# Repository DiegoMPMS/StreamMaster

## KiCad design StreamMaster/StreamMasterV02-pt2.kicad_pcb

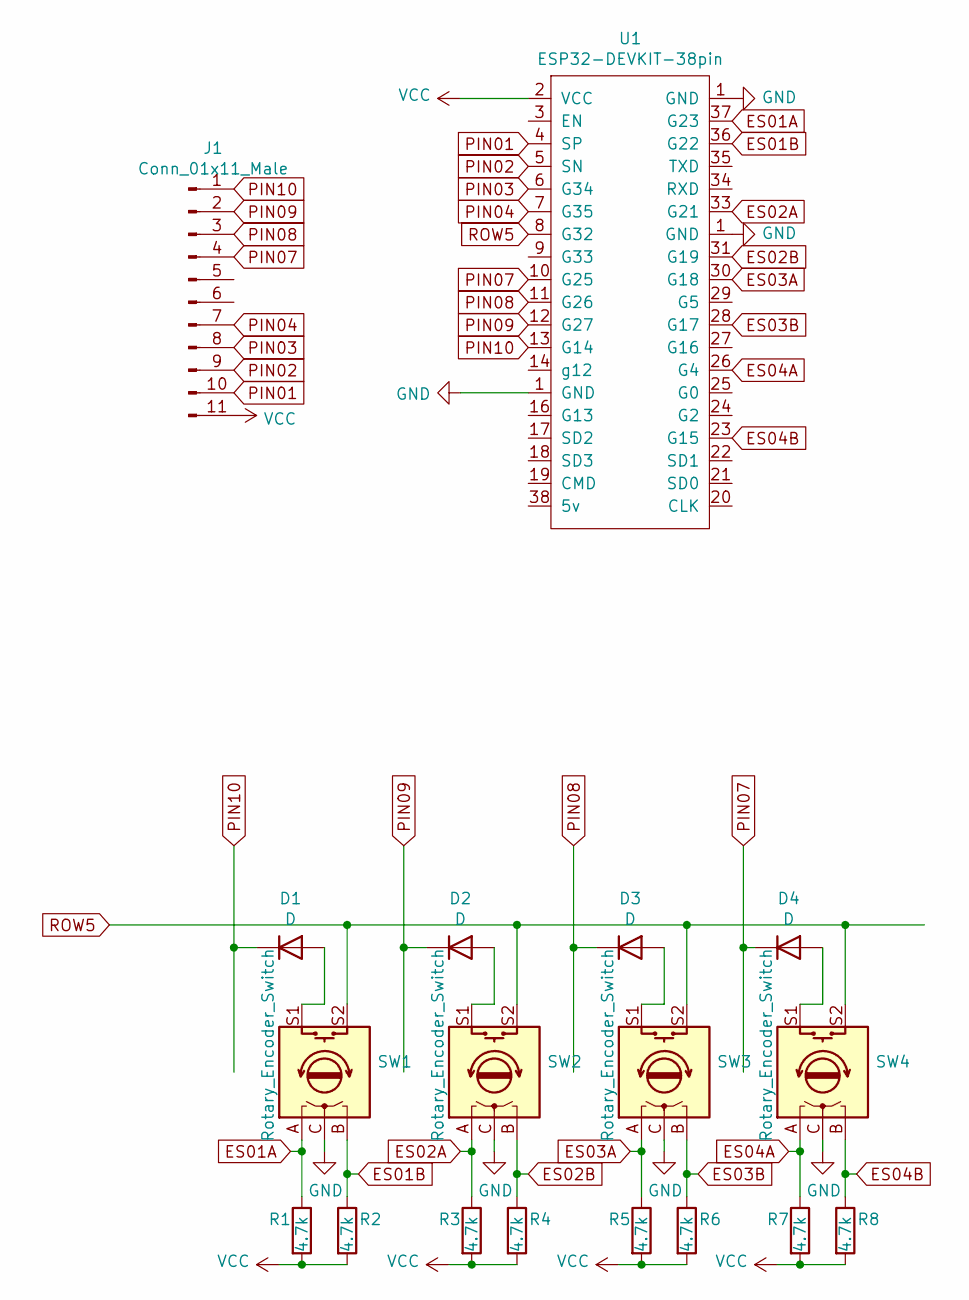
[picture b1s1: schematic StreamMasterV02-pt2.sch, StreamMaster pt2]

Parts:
D1, D2, D3, D4: D; D_SOD-323
J1: Conn_01x11_Male; PinHeader_1x11_P2.54mm_Horizontal
R1, R2, R3, R4, R5, R6, R7, R8: 4.7k; R_1206_3216Metric
SW1, SW2, SW3, SW4: Rotary_Encoder_Switch; RotaryEncoder_Alps_EC11E-Switch_Vertical_H20mm
U1: ESP32-DEVKIT-38pin; ESP32-Wroom-32-38pin

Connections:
ES01A: R1.1, SW1.A, U1.37 (G23)
ES01B: R2.1, SW1.B, U1.36 (G22)
ES02A: R3.1, SW2.A, U1.33 (G21)
ES02B: R4.1, SW2.B, U1.31 (G19)
ES03A: R5.1, SW3.A, U1.30 (G18)
ES03B: R6.1, SW3.B, U1.28 (G17)
ES04A: R7.1, SW4.A, U1.26 (G4)
ES04B: R8.1, SW4.B, U1.23 (G15)
GND: SW1.C, SW2.C, SW3.C, SW4.C, U1.1 (GND)
unnamed: D1.2 (A), SW1.S1
unnamed: D2.2 (A), SW2.S1
unnamed: D3.2 (A), SW3.S1
unnamed: D4.2 (A), SW4.S1
PIN01: J1.10, U1.4 (SP)
PIN02: J1.9, U1.5 (SN)
PIN03: J1.8, U1.6 (G34)
PIN04: J1.7, U1.7 (G35)
PIN07: D4.1 (K), J1.4, U1.10 (G25)
PIN08: D3.1 (K), J1.3, U1.11 (G26)
PIN09: D2.1 (K), J1.2, U1.12 (G27)
PIN10: D1.1 (K), J1.1, U1.13 (G14)
ROW5: SW1.S2, SW2.S2, SW3.S2, SW4.S2, U1.8 (G32)
VCC: J1.11, R1.2, R2.2, R3.2, R4.2, R5.2, R6.2, R7.2, R8.2, U1.2 (VCC)

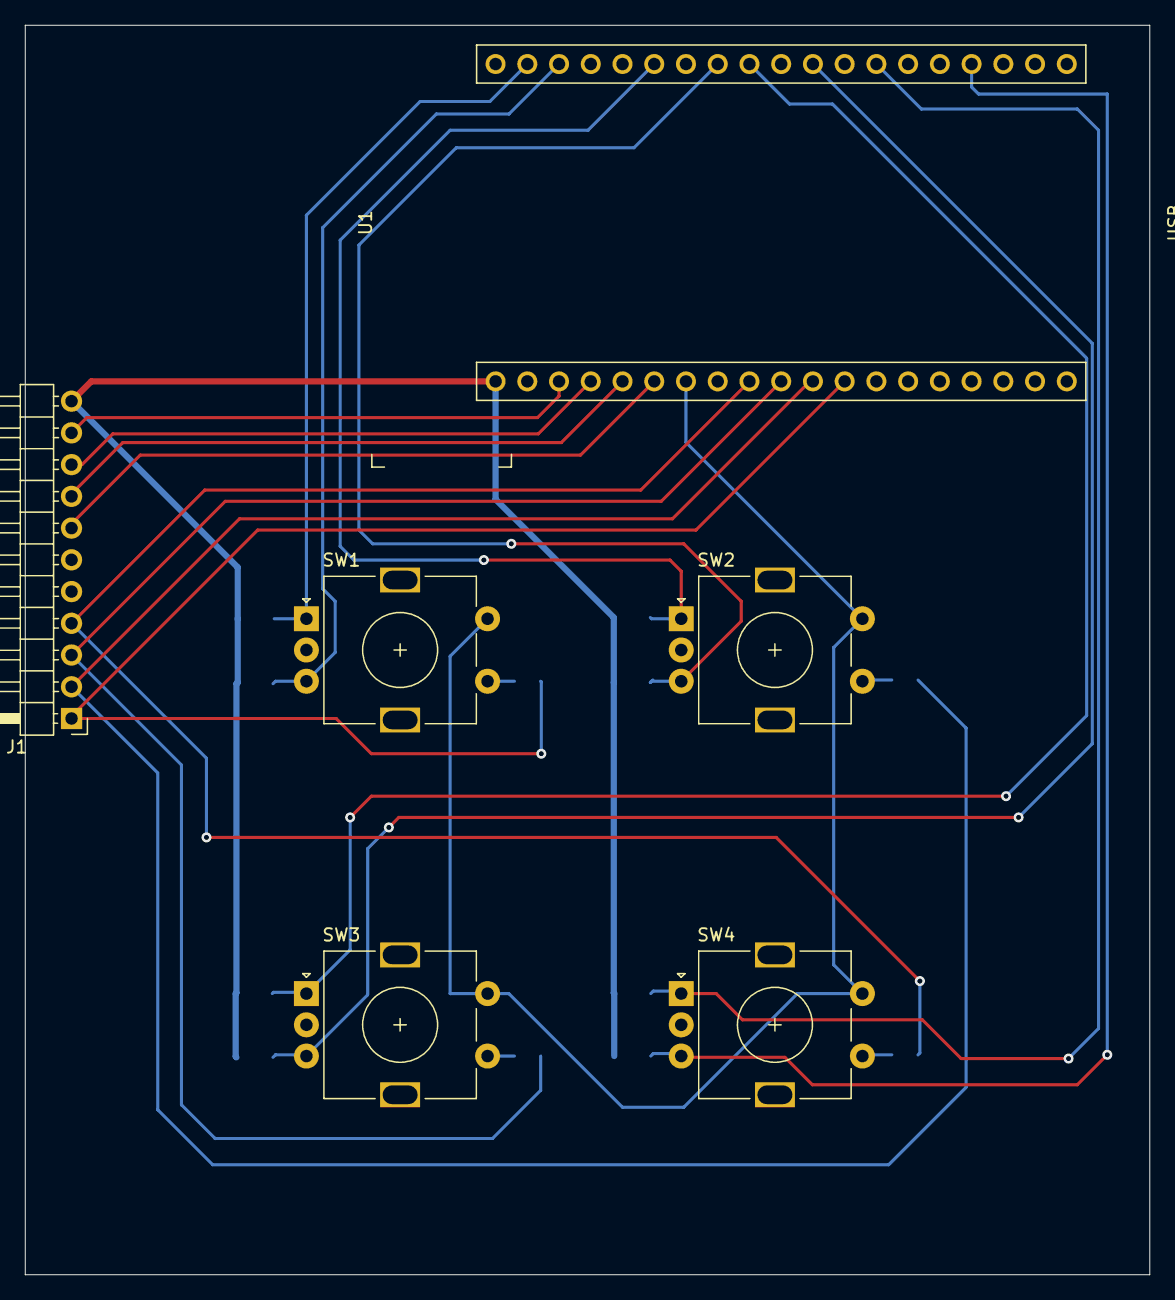
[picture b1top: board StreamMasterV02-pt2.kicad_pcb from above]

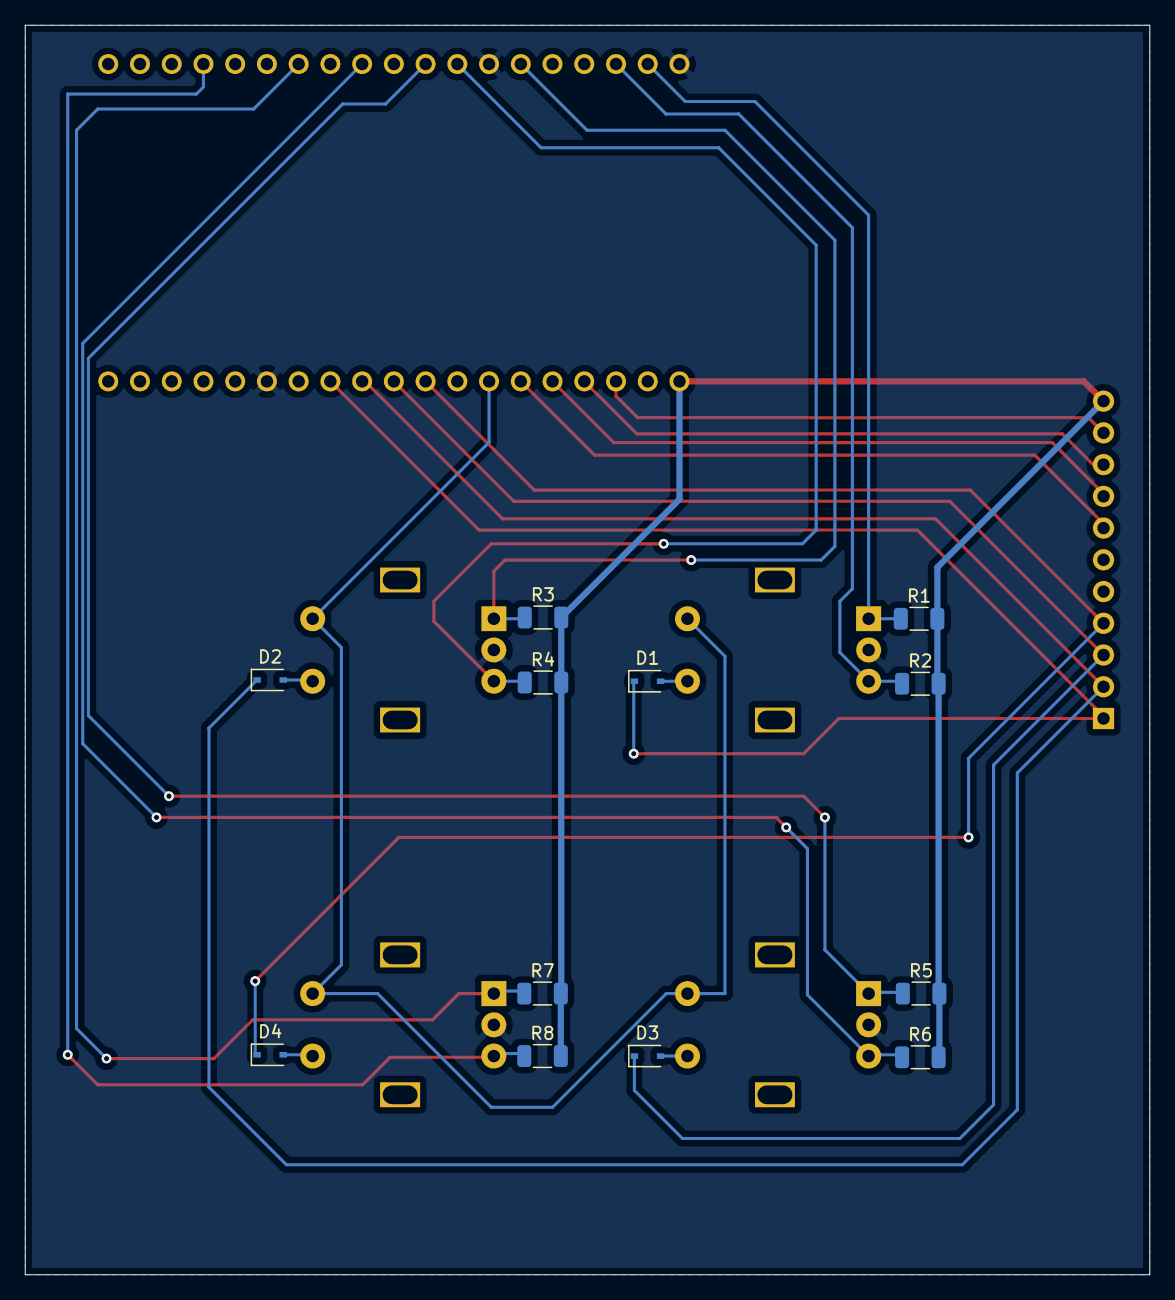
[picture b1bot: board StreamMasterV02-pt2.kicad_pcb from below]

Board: 2 copper layers, 90.0 x 100.0 mm, 18 parts (12 on the bottom side), 23 nets.

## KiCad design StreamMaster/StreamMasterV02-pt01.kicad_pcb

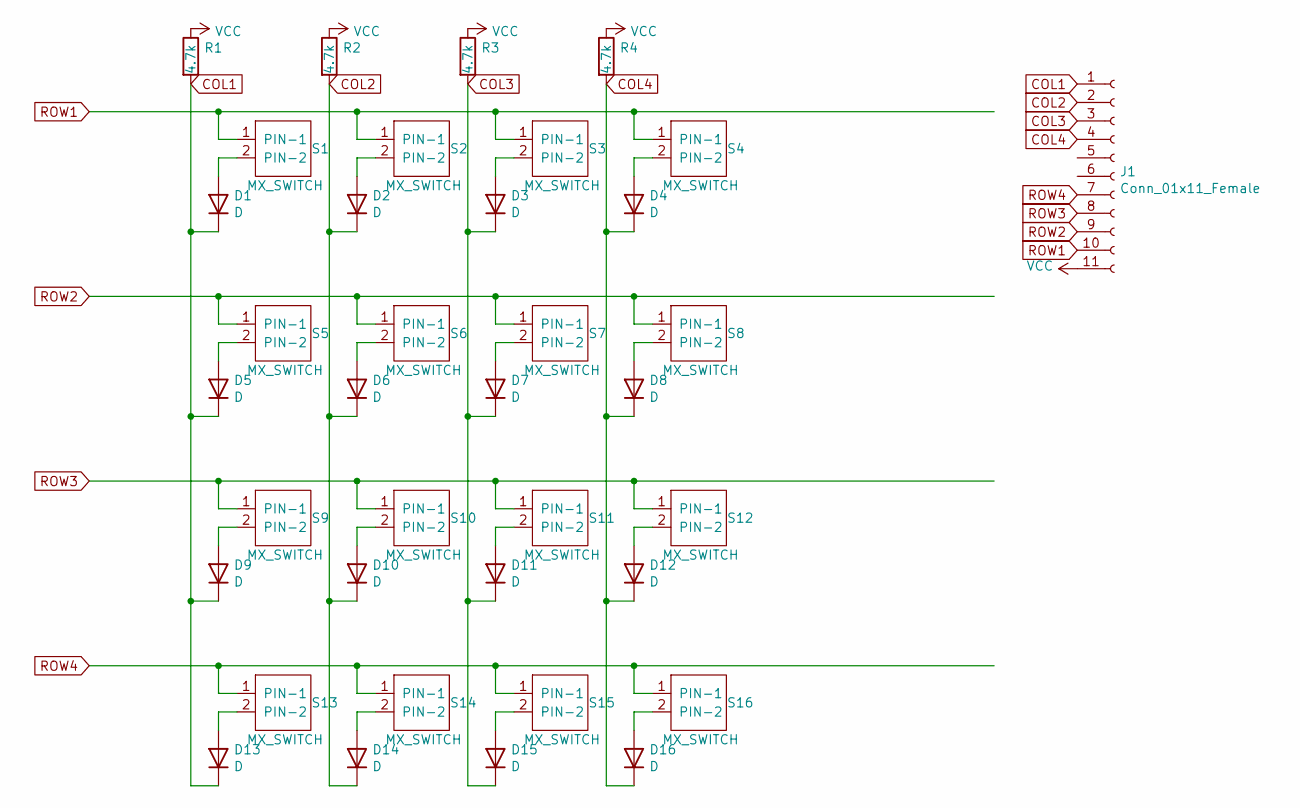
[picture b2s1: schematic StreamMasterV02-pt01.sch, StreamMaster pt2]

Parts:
D1, D2, D3, D4, D5, D6, D7, D8, D9, D10, D11, D12, D13, D14, D15, D16: D; D_SOD-323
J1: Conn_01x11_Female; PinSocket_1x11_P2.54mm_Horizontal
R1, R2, R3, R4: 4.7k; R_1206_3216Metric
S1, S2, S3, S4, S5, S6, S7, S8, S9, S10, S11, S12, S13, S14, S15, S16: MX_SWITCH; SW_Cherry_MX_1.00u_PCB

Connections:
COL1: D1.1 (K), D5.1 (K), D9.1 (K), D13.1 (K), J1.1, R1.2
COL2: D2.1 (K), D6.1 (K), D10.1 (K), D14.1 (K), J1.2, R2.2
COL3: D3.1 (K), D7.1 (K), D11.1 (K), D15.1 (K), J1.3, R3.2
COL4: D4.1 (K), D8.1 (K), D12.1 (K), D16.1 (K), J1.4, R4.2
unnamed: D1.2 (A), S1.2 (PIN-2)
unnamed: D2.2 (A), S2.2 (PIN-2)
unnamed: D3.2 (A), S3.2 (PIN-2)
unnamed: D4.2 (A), S4.2 (PIN-2)
unnamed: D5.2 (A), S5.2 (PIN-2)
unnamed: D6.2 (A), S6.2 (PIN-2)
unnamed: D7.2 (A), S7.2 (PIN-2)
unnamed: D8.2 (A), S8.2 (PIN-2)
unnamed: D9.2 (A), S9.2 (PIN-2)
unnamed: D10.2 (A), S10.2 (PIN-2)
unnamed: D11.2 (A), S11.2 (PIN-2)
unnamed: D12.2 (A), S12.2 (PIN-2)
unnamed: D13.2 (A), S13.2 (PIN-2)
unnamed: D14.2 (A), S14.2 (PIN-2)
unnamed: D15.2 (A), S15.2 (PIN-2)
unnamed: D16.2 (A), S16.2 (PIN-2)
ROW1: J1.10, S1.1 (PIN-1), S2.1 (PIN-1), S3.1 (PIN-1), S4.1 (PIN-1)
ROW2: J1.9, S5.1 (PIN-1), S6.1 (PIN-1), S7.1 (PIN-1), S8.1 (PIN-1)
ROW3: J1.8, S9.1 (PIN-1), S10.1 (PIN-1), S11.1 (PIN-1), S12.1 (PIN-1)
ROW4: J1.7, S13.1 (PIN-1), S14.1 (PIN-1), S15.1 (PIN-1), S16.1 (PIN-1)
VCC: J1.11, R1.1, R2.1, R3.1, R4.1

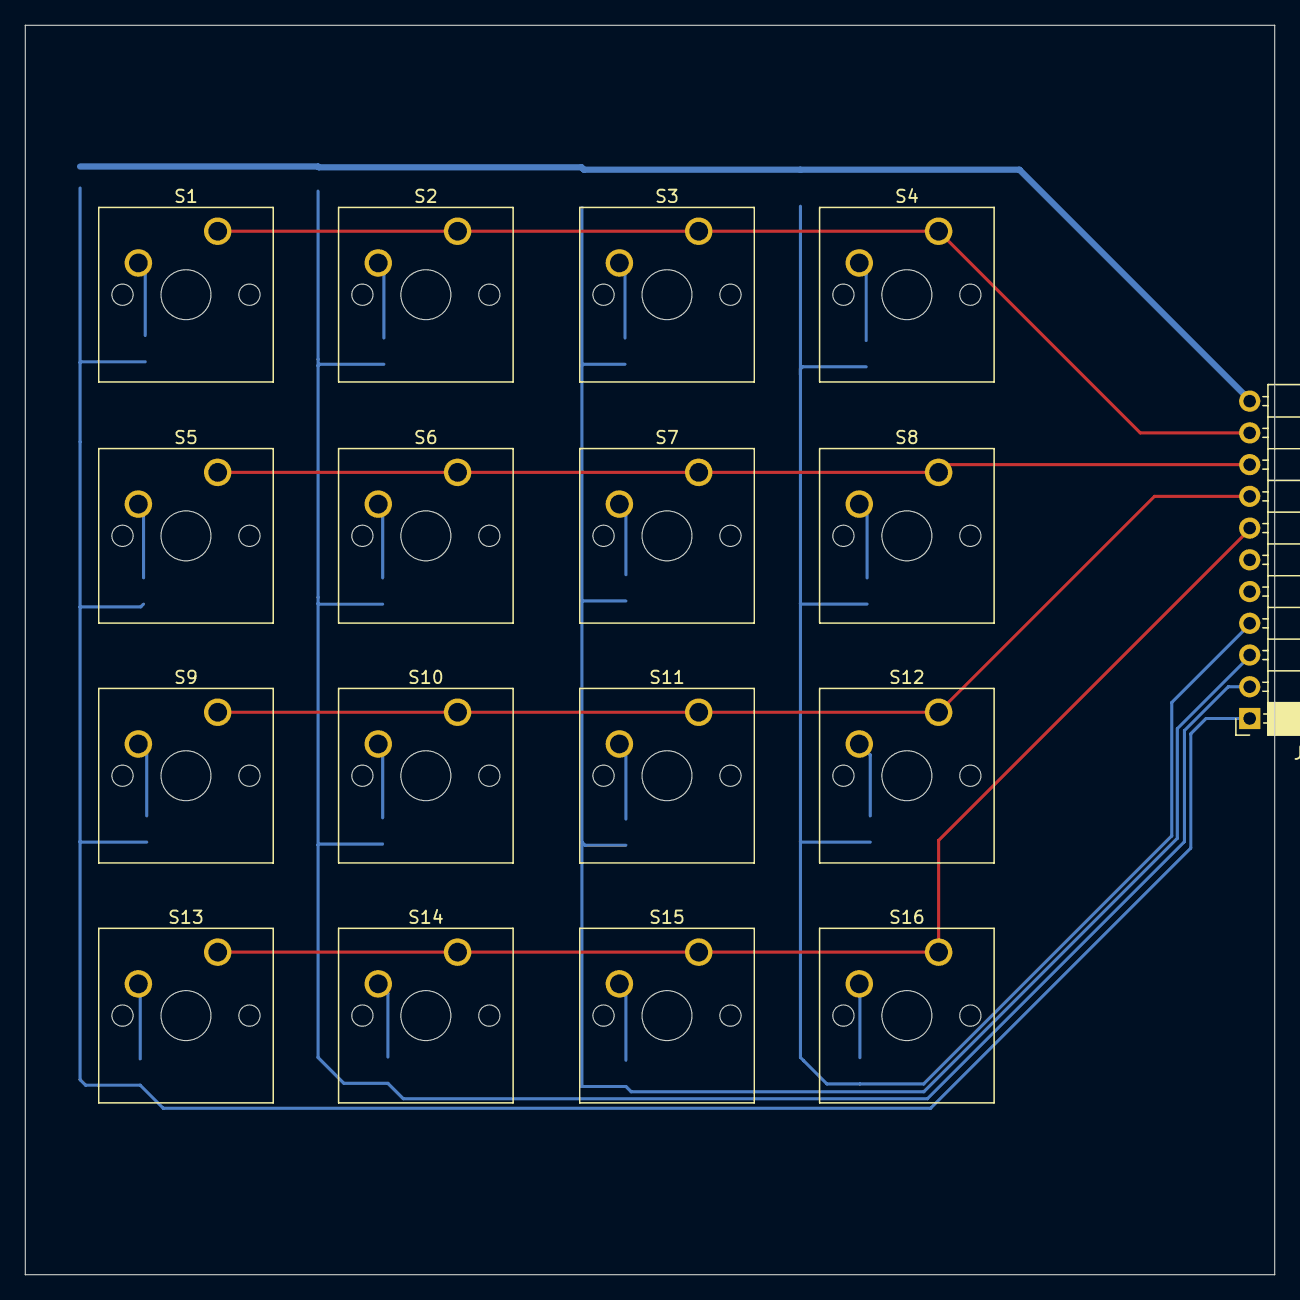
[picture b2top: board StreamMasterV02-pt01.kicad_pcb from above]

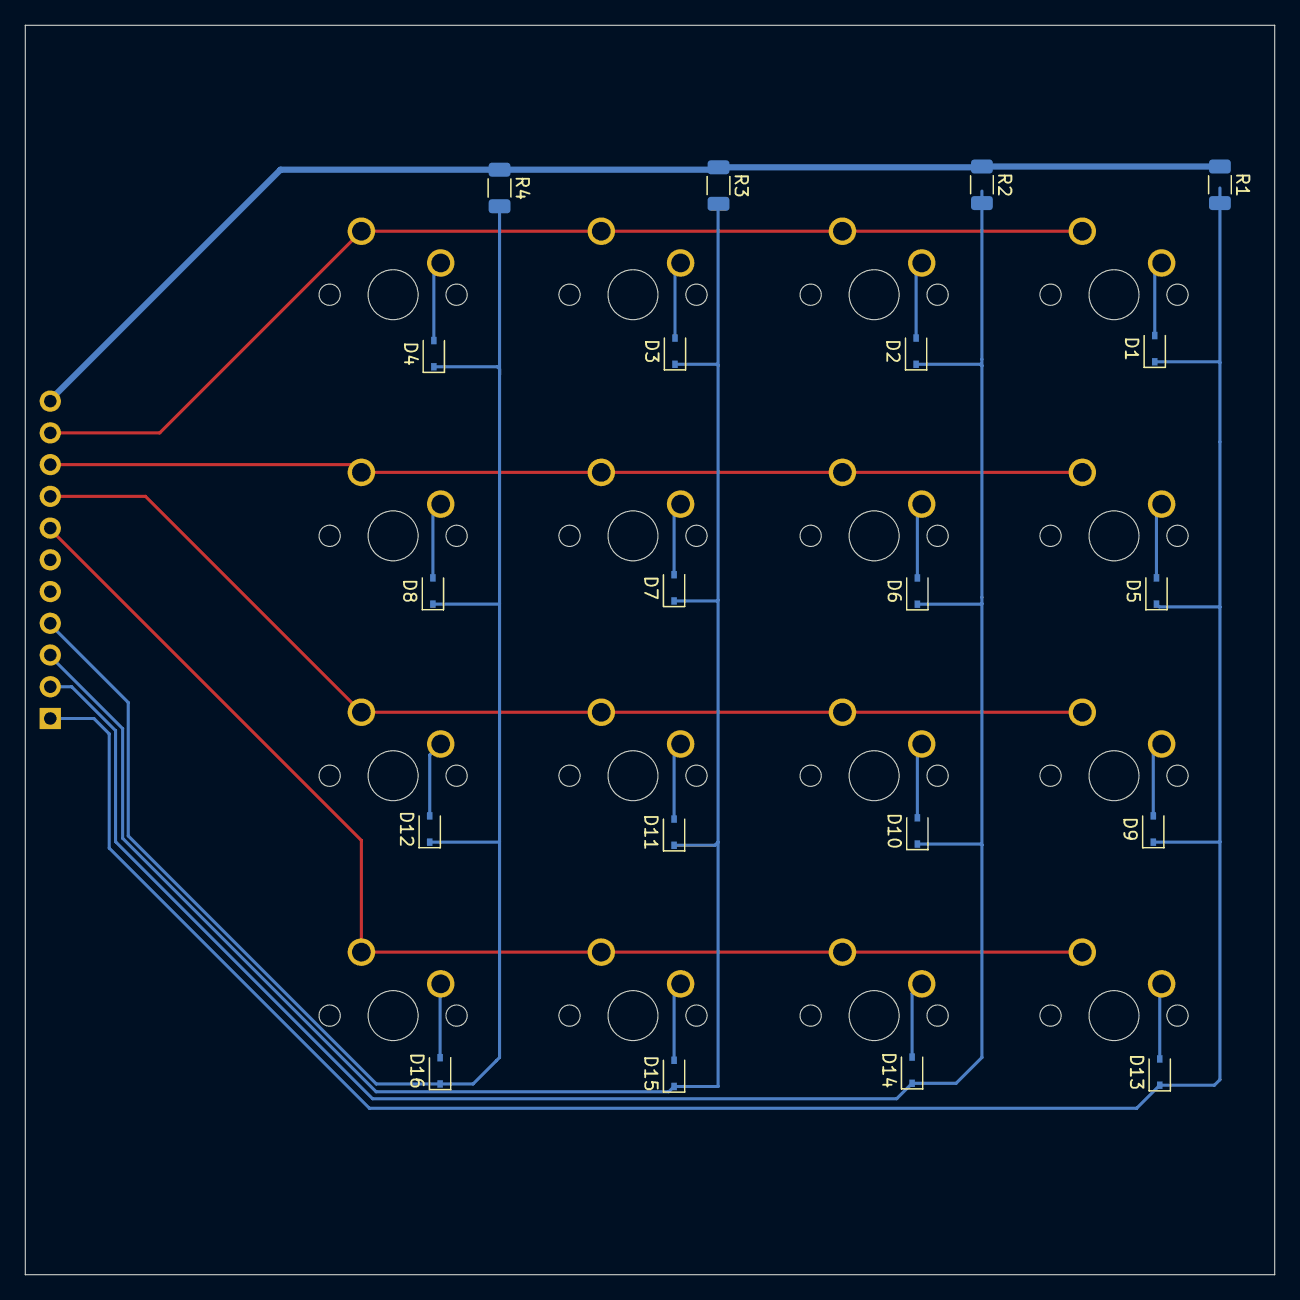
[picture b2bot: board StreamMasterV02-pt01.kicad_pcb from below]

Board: 2 copper layers, 100.0 x 100.0 mm, 37 parts (20 on the bottom side), 25 nets.

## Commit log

2021-09-08 First Commit, schematic do projeto de Teclado de Macros StreamMaster.
2021-09-14 14/set/2021 - PCB dividida em duas, modelos 3D para botões mecânicos, encoders, e esp32 foram adicionados.
